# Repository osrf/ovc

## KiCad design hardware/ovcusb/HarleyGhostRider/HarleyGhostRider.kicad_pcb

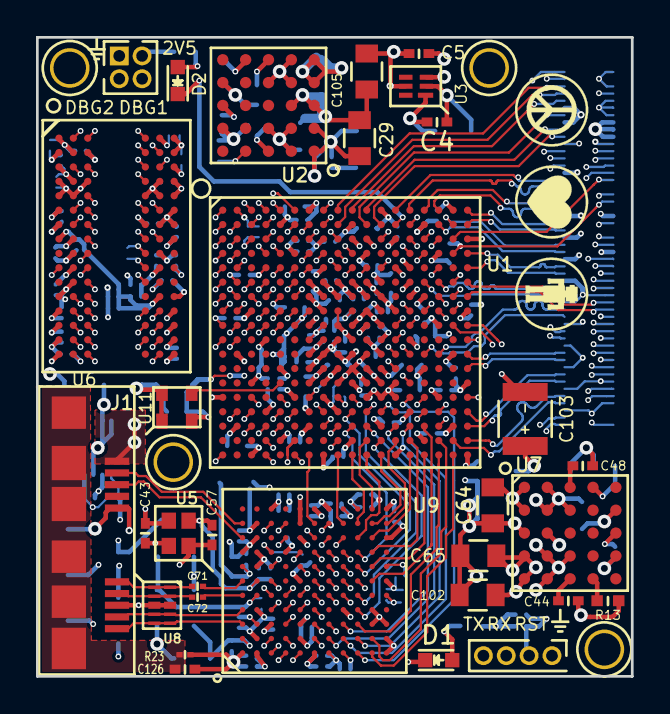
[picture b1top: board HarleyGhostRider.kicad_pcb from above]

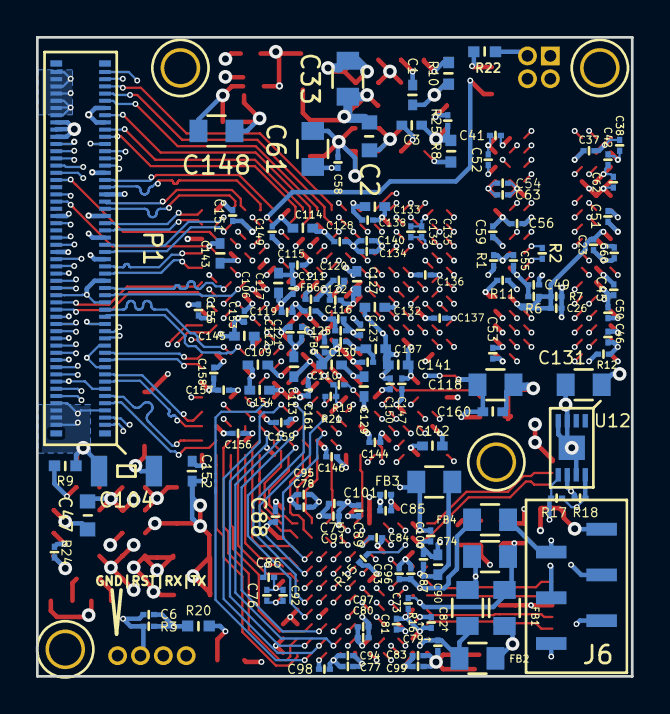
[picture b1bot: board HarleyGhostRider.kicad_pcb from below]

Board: 10 copper layers, 33.0 x 35.5 mm, 172 parts (141 on the bottom side), 210 nets.

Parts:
C1, C3, C44, C48, C160: 10n; C_0402
C2, C47: 10u; C_0603
C4, C5: 1u; C_0402
C6, C54, C56, C60, C111, C112, C115, C116, C117, C119, C120, C121, C122, C123, C124, C128, C130, C134, C135, C136, C137, C144, C146, C147, C149, C150, C151, C153, C155, C156, C157, C158, C159, C161: 470n; C_0201
C23, C58: 1u; C_0201
C26, C38, C42, C62, C63, C91, C92, C94, C95, C96, C97, C98, C99, C100, C101, C138, C139, C140: 10n; C_0201
C29, C33, C64, C65, C105, C118, C131, C148: 47u; C_0805
C37, C41, C45, C49, C51, C53: 2.2n; C_0201
C43, C57: 30p; C_0402
C46, C50, C52, C71, C72, C73, C75, C76, C77, C78, C79, C80, C81, C83, C84, C85, C86, C87, C88, C89, C93, C125: 100n; C_0201
C55: 3.3n; C_0201
C59: 4.7n; C_0201
C61, C74, C82, C102: 22u; C_0805
C90: 2.2u; C_0402
C103: 330u; C_1210Polarized
C104: 100u; C_1206
C106, C107, C109, C110, C113, C114, C127, C129, C132, C133, C141, C142, C143, C145, C152, C154: 4.7u; C_0402
C126: 4.7n; C_0402
D1: GREEN; LED_0603
D2: RED; LED_0603
FB1, FB2, FB3, FB4: 600; C_0805
FB5, FB6: 600; C_0201
J1: USB_3.1_microB; USB3_Micro-B
J3: CONN_01X04; Pin_Header_Straight_1x04_Pitch1.27mm
J6: CONN_01X06; GRPB061VWTC
P1: CONN_02X50; DF40C_100DP_0-4V
P2: CONN_02X02; Pin_Header_Straight_2x02_Pitch1.27mm
R1, R19, R21: 4.7k; C_0201
R2: 80.6; C_0201
R3, R17, R18: 10k; C_0201
R6, R7: 1k; C_0201
R8: 48.7k; R_0402
R9: 19.1k; R_0402
R10: 90.9k; R_0402
R11: 240; C_0201
R12: 2k; C_0201
R13: 60.4k; R_0402
R15: 6.04k; C_0201
R16: 200; C_0201
R20, R22: 200; R_0402
R23: 1M; C_0201
R24, R25: R; C_0201
U1: xc7a100tcsg324pkg; BGA324C80P18X18_1500X1500X150
U2, U7: LTM4622; LGA25_6.25X6.25X1.82
U3: TPS72718DSET; WSON6_15X15mm
U5: 8y-19.200MAAE; 8y
U6: MT41K128M16; WBGA96C80P6X16_800X1400X110
U8: IC10pins; 10-UFDFN
U9: CYUSB3014; BGA121C80P11X11_1000X1000X110
U11: OSCILLATOR; ASDMB
U12: 24LC128T-I/MNY; 8-TDFN_2x3_1EP

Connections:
+1V0: C33.2, C103.1, C104.1, C107.1, C110.1, C111.1, C113.1, C120.1, C121.1, C122.1, C123.1, C124.1, C127.1, C129.1, C130.1, C161.1, U1.F8, U1.F10, U1.G7, U1.G9, U1.G11, U1.H8, U1.J7, U1.J11, U1.K8, U1.L7, U1.L11, U1.M8, U1.M10, U1.N7, U1.N9, U1.N11, U2.D1, U2.E1
+1V2: C65.2, C76.1, C78.1, C81.1, C84.1, C86.1, C89.1, C92.1, C95.1, C98.1, C100.1, C102.1, FB1.1, FB2.1, FB3.1, U7.D1, U7.E1, U9.B10, U9.C3, U9.E9, U9.F11, U9.H1, U9.J11, U9.L5, U9.L7
+1V8: C5.1, C105.1, C106.1, C109.1, C112.1, C115.1, C117.1, C119.1, FB6.1, U1.F12, U1.H12, U1.K12, U1.M12, U3.5
+2V5: C4.1, C6.1, C64.2, C75.1, C77.1, C80.1, C83.1, C85.1, C88.1, C91.1, C94.1, C97.1, C99.1, C101.1, C114.1, C118.1, C128.1, C141.1, C142.1, C143.1, C144.1, C145.1, C146.1, C147.1, C148.1, C149.1, C150.1, C151.1, C152.1, C153.1, C154.1, C155.1, C156.1, C157.1, C158.1, C159.1, C160.1, FB4.1, J6.5, P1.82, P1.84, P1.86, P2.2, R3.1, R17.1, R18.1, R19.1, R20.1, R21.1, R22.1, U1.A17, U1.B10, U1.C13, U1.D16, U1.G15, U1.H18, U1.K4, U1.K14, U1.L17, U1.N3, U1.N13, U1.P6, U1.P8, U1.P11, U1.P12, U1.P13, U1.P16, U1.R9, U1.T2, U1.T12, U1.U5, U1.U15, U1.V8, U1.V18, U3.1, U3.3, U7.A1, U7.B1, U9.B1, U9.C11, U9.E3, U9.F1, U9.H4, U9.H11, U9.L9, U11.1, U11.4, U12.8
+5V: C2.2, C47.2, J1.1, P1.88, P1.90, P1.92, P1.94, P1.96, P1.98, P1.100, U2.A2, U2.B2, U2.B3, U2.D2, U2.D3, U2.E2, U7.A2, U7.B2, U7.B3, U7.D2, U7.D3, U7.E2, U9.E10, U9.E11
/Sheet56A15E50/AVDDQ: C87.1, C90.1, FB3.2, U9.A7
/Sheet56A15E50/CVDDQ: C93.1, C96.1, FB4.2, U9.B6
/Sheet56A15E50/USB_SS_TX+: C72.2, U9.A5
/Sheet56A15E50/USB_SS_TX-: C71.2, U9.A6
/Sheet56A15E50/VDDRX: C79.1, C82.1, FB2.2, U9.A2
/Sheet56A15E50/VDDTX: C73.1, C74.1, FB1.2, U9.B5
/Sheet56A15EBD/GND_ADC: FB5.1, U1.H9, U1.J9, U1.K10
Artix_FX3_CLK: U1.P3, U9.J6
DDR_A0: U1.G2, U6.N3
DDR_A1: U1.H5, U6.P7
DDR_A2: U1.G3, U6.P3
DDR_A3: U1.H2, U6.N2
DDR_A4: U1.J4, U6.P8
DDR_A5: U1.J2, U6.P2
DDR_A6: U1.G6, U6.R8
DDR_A7: U1.K1, U6.R2
DDR_A8: U1.H6, U6.T8
DDR_A9: U1.J3, U6.R3
DDR_A10: U1.F6, U6.L7
DDR_A11: U1.H4, U6.R7
DDR_A12: U1.G4, U6.N7
DDR_A13: U1.K2, U6.T3
DDR_BA0: U1.E1, U6.M2
DDR_BA1: U1.G1, U6.N8
DDR_BA2: U1.F1, U6.M3
DDR_CAS#: U1.C1, U6.K3
DDR_CKE: R1.1, U1.H1, U6.K9
DDR_CLK+: R2.1, U1.F4, U6.J7
DDR_CLK-: R2.2, U1.F3, U6.K7
DDR_DQL0: U1.B7, U6.E3
DDR_DQL1: U1.D8, U6.F7
DDR_DQL2: U1.C7, U6.F2
DDR_DQL3: U1.B6, U6.F8
DDR_DQL4: U1.E5, U6.H3
DDR_DQL5: U1.D7, U6.H8
DDR_DQL6: U1.E6, U6.G2
DDR_DQL7: U1.E7, U6.H7
DDR_DQSL+: U1.A6, U6.F3
DDR_DQSL-: U1.A5, U6.G3
DDR_DQSU+: U1.B1, U6.C7
DDR_DQSU-: U1.A1, U6.B7
DDR_DQU0: U1.B2, U6.D7
DDR_DQU1: U1.D4, U6.C3
DDR_DQU2: U1.B3, U6.C8
DDR_DQU3: U1.D5, U6.C2
DDR_DQU4: U1.B4, U6.A7
DDR_DQU5: U1.C4, U6.A2
DDR_DQU6: U1.A3, U6.B8
DDR_DQU7: U1.A4, U6.A3
DDR_ODT: U1.E2, U6.K1
DDR_RAS#: U1.C2, U6.J3
DDR_RST#: R12.2, U1.J5, U6.T2
DDR_VDD: C29.2, C37.1, C38.1, C41.1, C42.1, C45.1, C46.1, C49.1, C50.1, C51.1, C52.1, C53.1, C54.1, C55.1, C56.1, C58.1, C59.1, C60.1, C61.1, C62.1, C63.1, C131.1, C132.1, C133.1, C134.1, C135.1, C136.1, C137.1, C138.1, C139.1, C140.1, R6.1, R12.1, U1.A7, U1.C3, U1.D6, U1.F2, U1.G5, U1.J1, U2.A1, U2.B1, U6.A1, U6.A8, U6.B2, U6.C1, U6.C9, U6.D2, U6.D9, U6.E9, U6.F1, U6.G7, U6.H2, U6.H9, U6.K2, U6.K8, U6.N1, U6.N9, U6.R1, U6.R9
DDR_VREF: C23.1, C26.1, R6.2, R7.1, U6.H1, U6.M8
DDR_WE#: U1.D2, U6.L3
FLASH_SCL: R18.2, U9.D10, U12.6
FLASH_SDA: R17.2, U9.D9, U12.5
FPGA_CLK: U1.N5, U11.3
FPGA_DEBUG1: P2.4, U1.C9
FPGA_DEBUG2: P2.3, U1.D10
FPGA_JTAG_TCK: P1.54, U1.E10
FPGA_JTAG_TDI: P1.60, U1.E11
FPGA_JTAG_TDO: P1.58, U1.E13
FPGA_JTAG_TMS: P1.52, U1.E12
FPGA_LED: D2.1, U1.B13
FPGA_SS_CCLK: U1.E9, U9.D2
FPGA_SS_DIN: U1.K18, U9.D1
FPGA_SS_DONE: U1.P10, U9.C4
FPGA_SS_DOUT: U1.T16, U9.C1
FPGA_SS_INIT_B: R19.2, U1.P7, U9.D3
FPGA_SS_PROGRAM_B: R21.2, U1.P9, U9.D4
FPGA_Signal1: P1.64, U1.D17
FPGA_Signal2: P1.66, U1.E16
FPGA_Signal3: P1.70, U1.C17
FPGA_Signal4: P1.72, U1.D15
FPGA_Signal5: P1.74, U1.F14
FPGA_Signal6: P1.76, U1.C10
FPGA_Signal7: P1.78, U1.C12
FX3_A0: U1.T9, U9.H5
FX3_A1: U1.R11, U9.J5
FX3_DQ0: U1.V7, U9.F10
FX3_DQ1: U1.R3, U9.F9
FX3_DQ2: U1.R2, U9.F7
FX3_DQ3: U1.V4, U9.G10
FX3_DQ4: U1.T4, U9.G9
FX3_DQ5: U1.T3, U9.F8
FX3_DQ6: U1.V9, U9.H10
FX3_DQ7: U1.U6, U9.H9
FX3_DQ8: U1.V10, U9.J10
FX3_DQ9: U1.V11, U9.J9
FX3_DQ10: U1.U11, U9.K11
FX3_DQ11: U1.U13, U9.L10
FX3_DQ12: U1.V12, U9.K10
FX3_DQ13: U1.V14, U9.K9
FX3_DQ14: U1.T10, U9.J8
FX3_DQ15: U1.T5, U9.G8
FX3_DQ16: U1.U16, U9.K2
FX3_DQ17: U1.U12, U9.J4
FX3_DQ18: U1.V17, U9.K1
FX3_DQ19: U1.T14, U9.J2
FX3_DQ20: U1.V16, U9.J3
FX3_DQ21: U1.P14, U9.J1
FX3_DQ22: U1.R12, U9.H2
FX3_DQ23: U1.T11, U9.H3
FX3_DQ24: U1.P5, U9.F4
FX3_DQ25: U1.T13, U9.G2
FX3_DQ26: U1.R8, U9.G3
FX3_DQ27: U1.L14, U9.F3
FX3_DQ28: U1.U4, U9.F5
FX3_DQ29: U1.P18, U9.E1
FX3_DQ30: U1.V1, U9.E5
FX3_DQ31: U1.R16, U9.E4
FX3_FLAGA: U1.V6, U9.G7
FX3_FLAGB: U1.U9, U9.G6
FX3_FLAGC: U1.T15, U9.K6
FX3_FLAGD: U1.T8, U9.G5
FX3_JTAG_TCK: J6.1, U9.F6
FX3_JTAG_TDI: J6.2, U9.E7
FX3_JTAG_TDO: J6.4, U9.C10
FX3_JTAG_TMS: J6.3, U9.E8
FX3_LED/DEBUG: D1.1, U9.F2
FX3_PKT_END#: U1.R5, U9.H8
FX3_RST#: C6.2, J3.2, R3.2, U9.C5
FX3_SLCS#: U1.U14, U9.K8
FX3_SLOE#: U1.R10, U9.J7
FX3_SLRD#: U1.R6, U9.H7
FX3_SLWR#: U1.V15, U9.K7
FX3_UART_RX: J3.3, U9.D5
FX3_UART_TX: J3.4, U9.C2
GND: C1.2, C2.1, C3.2, C4.2, C5.2, C23.2, C26.2, C29.1, C33.1, C37.2, C38.2, C41.2, C42.2, C43.2, C44.2, C45.2, C46.2, C47.1, C48.2, C49.2, C50.2, C51.2, C52.2, C53.2, C54.2, C55.2, C56.2, C57.2, C58.2, C59.2, C60.2, C61.2, C62.2, C63.2, C64.1, C65.1, C73.2, C74.2, C75.2, C76.2, C77.2, C78.2, C79.2, C80.2, C81.2, C82.2, C83.2, C84.2, C85.2, C86.2, C87.2, C88.2, C89.2, C90.2, C91.2, C92.2, C93.2, C94.2, C95.2, C96.2, C97.2, C98.2, C99.2, C100.2, C101.2, C102.2, C103.2, C104.2, C105.2, C106.2, C107.2, C109.2, C110.2, C111.2, C112.2, C113.2, C114.2, C115.2, C116.2, C117.2, C118.2, C119.2, C120.2, C121.2, C122.2, C123.2, C124.2, C125.2, C126.2, C127.2, C128.2, C129.2, C130.2, C131.2, C132.2, C133.2, C134.2, C135.2, C136.2, C137.2, C138.2, C139.2, C140.2, C141.2, C142.2, C143.2, C144.2, C145.2, C146.2, C147.2, C148.2, C149.2, C150.2, C151.2, C152.2, C153.2, C154.2, C155.2, C156.2, C157.2, C158.2, C159.2, C160.2, C161.2, FB5.2, J1.5, J1.8, J3.1, J6.6, P1.2, P1.4, P1.5, P1.6, P1.8, P1.11, P1.14, P1.17, P1.20, P1.23, P1.26, P1.29, P1.32, P1.35, P1.38, P1.41, P1.44, P1.47, P1.50, P1.53, P1.59, P1.65, P1.71, P1.80, P1.85, P1.89, P2.1, R1.2, R7.2, R8.2, R9.2, R10.2, R11.2, R13.2, R15.2, R16.2, R23.2, R24.2, R25.2, U1.A2, U1.A12, U1.B5, U1.B15, U1.C8, U1.C18, U1.D1, U1.D11, U1.E4, U1.E8, U1.E14, U1.F7, U1.F9, U1.F11, U1.F17, U1.G8, U1.G10, U1.G12, U1.H3, U1.H7, U1.H11, U1.H13, U1.J6, U1.J8, U1.J10, U1.J12, U1.J16, U1.K7, U1.K9, U1.K11, U1.L2, U1.L8, U1.L9, U1.L10, U1.L12, U1.M5, U1.M7, U1.M9, U1.M11, U1.M15, U1.N8, U1.N10, U1.N12, U1.N18, U1.P1, U1.R4, U1.R14, U1.T7, U1.T17, U1.U10, U1.V3, U1.V13, U2.B5, U2.C1, U2.C2, U2.D5, U3.2, U5.2, U5.4, U6.A9, U6.B1, U6.B3, U6.B9, U6.D1, U6.D3, U6.D8, U6.E1, U6.E2, U6.E7, U6.E8, U6.F9, U6.G1, U6.G8, U6.G9, U6.J2, U6.J8, U6.L2, U6.M1, U6.M9, U6.P1, U6.P9, U6.T1, U6.T9, U7.B5, U7.C1, U7.C2, U7.D5, U8.3, U8.8, U9.A1, U9.A8, U9.B2, U9.B4, U9.B7, U9.B8, U9.B9, U9.D8, U9.E2, U9.E6, U9.G1, U9.G11, U9.K3, U9.K4, U9.L1, U9.L2, U9.L3, U9.L6, U9.L11, U11.2, U12.3, U12.4, U12.7, U12.EPAD
IMU_CS#: P1.77, U1.C16
unnamed: C1.1, U2.E3
unnamed: C3.1, U2.A3
unnamed: C43.1, U5.3, U9.C7
unnamed: C44.1, U7.E3
unnamed: C48.1, U7.A3
unnamed: C57.1, U5.1, U9.C6
unnamed: C116.1, C125.1, FB6.2, U1.H10
unnamed: C126.1, J1.SHLD, R23.1
unnamed: D1.2, R20.2
unnamed: D2.2, R22.2
unnamed: R8.1, U2.A4
unnamed: R9.1, U7.A4
unnamed: R10.1, U2.E4
unnamed: R11.1, U6.L8
unnamed: R13.1, U7.E4
unnamed: R15.1, U9.C8
unnamed: R16.1, U9.B3
unnamed: R24.1, U7.C5
unnamed: R25.1, U2.C5
Python1_CS#: P1.81, U1.B12
Python1_DOUT0+: P1.43, U1.E18
Python1_DOUT0-: P1.45, U1.D18
Python1_DOUT1+: P1.49, U1.B16
Python1_DOUT1-: P1.51, U1.B17
Python1_DOUT2+: P1.55, U1.B18
Python1_DOUT2-: P1.57, U1.A18
Python1_DOUT3+: P1.61, U1.A16
Python1_DOUT3-: P1.63, U1.A15
Python1_Monitor: P1.95, U1.A9
Python1_SYNC+: P1.67, U1.A14
Python1_SYNC-: P1.69, U1.A13
Python1_clk_return+: P1.37, U1.F15
Python1_clk_return-: P1.39, U1.F16
Python2_CS#: P1.83, U1.A11
Python2_DOUT0+: P1.18, U1.J18
Python2_DOUT0-: P1.16, U1.J17
Python2_DOUT1+: P1.12, U1.J13
Python2_DOUT1-: P1.10, U1.K13
Python2_DOUT2+: P1.22, U1.H17
Python2_DOUT2-: P1.24, U1.G17
Python2_DOUT3+: P1.28, U1.J14
Python2_DOUT3-: P1.30, U1.H15
Python2_Monitor: P1.97, U1.B8
Python2_SYNC+: P1.36, U1.F18
Python2_SYNC-: P1.34, U1.G18
Python2_clk_return+: P1.40, U1.H16
Python2_clk_return-: P1.42, U1.G16
Python3_CS#: P1.79, U1.B14
Python3_DOUT0+: P1.7, U1.U17
Python3_DOUT0-: P1.9, U1.U18
Python3_DOUT1+: P1.13, U1.T18
Python3_DOUT1-: P1.15, U1.R18
Python3_DOUT2+: P1.33, U1.L16
Python3_DOUT2-: P1.31, U1.L15
Python3_DOUT3+: P1.27, U1.L13
Python3_DOUT3-: P1.25, U1.M13
Python3_Monitor: P1.99, U1.A8
Python3_SYNC+: P1.21, U1.L18
Python3_SYNC-: P1.19, U1.M18
Python3_clk_return+: P1.3, U1.P15
Python3_clk_return-: P1.1, U1.R15
Python_RST#: P1.73, U1.D9
Python_Trigger: P1.75, U1.C15
Python_lvds_clk+: P1.46, U1.D14
Python_lvds_clk-: P1.48, U1.C14
SPI_MISO: P1.93, U1.B9
SPI_MOSI: P1.91, U1.A10
SPI_SCK: P1.87, U1.B11
SS_RX+: J1.10, U8.5, U8.6, U9.A3
SS_RX-: J1.9, U8.4, U8.7, U9.A4
SS_TX+: C72.1, J1.7, U8.2, U8.9
SS_TX-: C71.1, J1.6, U8.1, U8.10
USB_HS_D+: J1.3, U9.A9
USB_HS_D-: J1.2, U9.A10

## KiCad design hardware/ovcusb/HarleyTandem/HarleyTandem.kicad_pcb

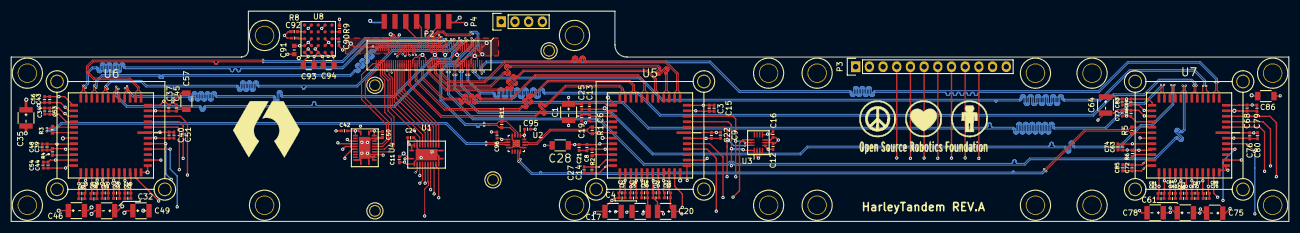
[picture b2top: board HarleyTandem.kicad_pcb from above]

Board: 6 copper layers, 237.0 x 39.0 mm, 115 parts (1 on the bottom side), 91 nets.

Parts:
C1, C4, C17, C20, C32, C35, C46, C49, C61, C64, C75, C78: 100u; C_1210Polarized
C2, C5, C7, C10, C15, C19, C21, C22, C25, C27, C30, C33, C36, C38, C41, C45, C48, C51, C53, C54, C56, C59, C62, C65, C67, C70, C74, C77, C79, C80, C83, C85, C88: 4.7u; C_0402
C3, C6, C8, C11, C12, C16, C24, C34, C37, C39, C42, C50, C63, C66, C68: 100n; C_0402
C9, C13, C14, C18, C23, C26, C29, C31, C40, C43, C44, C47, C52, C55, C58, C60, C69, C72, C73, C76, C81, C84, C87, C89, C95, C96: 1u; C_0402
C28, C57, C86: 10u; C_1206
C90, C92: 10n; C_0402
C91: 10u; C_0603
C93, C94: 47u; C_0805
P1: CONN_02X07; CustomJTAG
P2: CONN_02X50; DF40C_100DS_0-4V
P3: CONN_01X12; Pin_Header_Straight_1x12
P4: CONN_01X04; Pin_Header_Straight_1x04
R1, R3, R5, R11: 100; R_0402
R2, R4, R6: 47k; R_0402
R8: 13.3k; R_0402
R9: 30.1k; R_0402
U1, U4: 74AVCH8T245-1EP; QFN-24-1EP-Pitch0.5-nonSquare
U2: SI53306; QFN-16-1EP_3x3mm_Pitch0.5mm
U3: ST_LSM6DS3; LGA14_2.5X3X0.86
U5, U6, U7: NOIP1SN1300A-QDI; LCC101.6P1422X1422X165-48
U8: LTM4622; LGA25_6.25X6.25X1.82

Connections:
+1V8: C3.1, C6.1, C8.1, C15.1, C16.1, C19.1, C21.1, C28.1, C34.1, C37.1, C39.1, C45.1, C48.1, C53.1, C57.1, C63.1, C66.1, C68.1, C74.1, C77.1, C79.1, C86.1, C94.2, P4.3, U3.8, U5.6, U5.22, U5.26, U6.6, U6.22, U6.26, U7.6, U7.22, U7.26, U8.D1, U8.E1
+2V5: C24.1, C50.1, C95.2, C96.1, P1.2, P2.81, P2.83, P2.85, P3.3, U1.23, U1.24, U2.1, U2.5, U2.16, U4.23, U4.24
+3V3: C1.1, C2.1, C4.1, C5.1, C7.1, C9.1, C10.1, C11.1, C12.1, C13.1, C14.1, C17.1, C18.1, C20.1, C22.1, C23.1, C25.1, C26.1, C27.1, C29.1, C30.1, C31.1, C32.1, C33.1, C35.1, C36.1, C38.1, C40.1, C41.1, C42.1, C43.1, C44.1, C46.1, C47.1, C49.1, C51.1, C52.1, C54.1, C55.1, C56.1, C58.1, C59.1, C60.1, C61.1, C62.1, C64.1, C65.1, C67.1, C69.1, C70.1, C72.1, C73.1, C75.1, C76.1, C78.1, C80.1, C81.1, C83.1, C84.1, C85.1, C87.1, C88.1, C89.1, C93.2, P3.2, P4.2, U1.1, U3.5, U4.1, U4.2, U5.1, U5.19, U5.29, U5.31, U5.33, U5.36, U5.38, U5.40, U6.1, U6.19, U6.29, U6.31, U6.33, U6.36, U6.38, U6.40, U7.1, U7.19, U7.29, U7.31, U7.33, U7.36, U7.38, U7.40, U8.A1, U8.B1
+5V: C91.2, P2.87, P2.89, P2.91, P2.93, P2.95, P2.97, P2.99, P3.1, P4.1, U8.A2, U8.B2, U8.B3, U8.D2, U8.D3, U8.E2
FPGA_JTAG_TCK: P1.6, P2.53
FPGA_JTAG_TDI: P1.10, P2.59
FPGA_JTAG_TDO: P1.8, P2.57
FPGA_JTAG_TMS: P1.4, P2.51
FPGA_Signal1: P2.63, P3.4
FPGA_Signal2: P2.65, P3.5
FPGA_Signal3: P2.69, P3.6
FPGA_Signal4: P2.71, P3.7
FPGA_Signal5: P2.73, P3.8
FPGA_Signal6: P2.75, P3.9
FPGA_Signal7: P2.77, P3.10
GND: C1.2, C2.2, C3.2, C4.2, C5.2, C6.2, C7.2, C8.2, C9.2, C10.2, C11.2, C12.2, C13.2, C14.2, C15.2, C16.2, C17.2, C18.2, C19.2, C20.2, C21.2, C22.2, C23.2, C24.2, C25.2, C26.2, C27.2, C28.2, C29.2, C30.2, C31.2, C32.2, C33.2, C34.2, C35.2, C36.2, C37.2, C38.2, C39.2, C40.2, C41.2, C42.2, C43.2, C44.2, C45.2, C46.2, C47.2, C48.2, C49.2, C50.2, C51.2, C52.2, C53.2, C54.2, C55.2, C56.2, C57.2, C58.2, C59.2, C60.2, C61.2, C62.2, C63.2, C64.2, C65.2, C66.2, C67.2, C68.2, C69.2, C70.2, C72.2, C73.2, C74.2, C75.2, C76.2, C77.2, C78.2, C79.2, C80.2, C81.2, C83.2, C84.2, C85.2, C86.2, C87.2, C88.2, C89.2, C90.2, C91.1, C92.2, C93.1, C94.1, C95.1, C96.2, P1.1, P1.3, P1.5, P1.7, P1.9, P1.11, P1.13, P2.1, P2.3, P2.5, P2.6, P2.7, P2.12, P2.13, P2.18, P2.19, P2.24, P2.25, P2.30, P2.31, P2.36, P2.37, P2.42, P2.43, P2.48, P2.49, P2.54, P2.60, P2.66, P2.72, P2.79, P2.86, P2.90, P3.11, P3.12, P4.4, R2.2, R4.2, R6.2, R8.2, R9.2, U1.2, U1.11, U1.12, U1.13, U1.22, U1.25, U2.4, U2.8, U2.13, U2.17, U3.2, U3.3, U3.6, U3.7, U4.11, U4.12, U4.13, U4.14, U4.15, U4.16, U4.21, U4.22, U4.25, U5.5, U5.20, U5.21, U5.25, U5.27, U5.30, U5.32, U5.34, U5.35, U5.37, U5.39, U5.42, U5.43, U5.48, U6.5, U6.20, U6.21, U6.25, U6.27, U6.30, U6.32, U6.34, U6.35, U6.37, U6.39, U6.42, U6.43, U6.48, U7.5, U7.20, U7.21, U7.25, U7.27, U7.30, U7.32, U7.34, U7.35, U7.37, U7.39, U7.42, U7.43, U7.48, U8.B5, U8.C1, U8.C2, U8.D5
IMU_CS#: P2.78, U1.16
IMU_CS#_3V3: U1.8, U3.12
unnamed: C90.1, U8.E3
unnamed: C92.1, U8.A3
unnamed: R2.1, U5.28
unnamed: R4.1, U6.28
unnamed: R6.1, U7.28
unnamed: R8.1, U8.A4
unnamed: R9.1, U8.E4
Python1_CS#: P2.82, U1.18
Python1_CS#_3V3: U1.6, U5.47
Python1_DOUT0+: P2.44, U5.9
Python1_DOUT0-: P2.46, U5.10
Python1_DOUT1+: P2.50, U5.11
Python1_DOUT1-: P2.52, U5.12
Python1_DOUT2+: P2.56, U5.13
Python1_DOUT2-: P2.58, U5.14
Python1_DOUT3+: P2.62, U5.15
Python1_DOUT3-: P2.64, U5.16
Python1_Monitor: P2.96, U4.18
Python1_Monitor_3V3: U4.6, U5.44
Python1_SYNC+: P2.68, U5.17
Python1_SYNC-: P2.70, U5.18
Python1_clk_return+: P2.38, U5.7
Python1_clk_return-: P2.40, U5.8
Python1_lvds_clk+: R1.2, U2.14, U5.24
Python1_lvds_clk-: R1.1, U2.15, U5.23
Python2_CS#: P2.84, U1.19
Python2_CS#_3V3: U1.5, U6.47
Python2_DOUT0+: P2.17, U6.9
Python2_DOUT0-: P2.15, U6.10
Python2_DOUT1+: P2.11, U6.11
Python2_DOUT1-: P2.9, U6.12
Python2_DOUT2+: P2.21, U6.13
Python2_DOUT2-: P2.23, U6.14
Python2_DOUT3+: P2.27, U6.15
Python2_DOUT3-: P2.29, U6.16
Python2_Monitor: P2.98, U4.19
Python2_Monitor_3V3: U4.5, U6.44
Python2_SYNC+: P2.35, U6.17
Python2_SYNC-: P2.33, U6.18
Python2_clk_return+: P2.39, U6.7
Python2_clk_return-: P2.41, U6.8
Python2_lvds_clk+: R3.2, U2.7, U6.24
Python2_lvds_clk-: R3.1, U2.6, U6.23
Python3_CS#: P2.80, U1.17
Python3_CS#_3V3: U1.7, U7.47
Python3_DOUT0+: P2.8, U7.9
Python3_DOUT0-: P2.10, U7.10
Python3_DOUT1+: P2.14, U7.11
Python3_DOUT1-: P2.16, U7.12
Python3_DOUT2+: P2.34, U7.13
Python3_DOUT2-: P2.32, U7.14
Python3_DOUT3+: P2.28, U7.15
Python3_DOUT3-: P2.26, U7.16
Python3_Monitor: P2.100, U4.20
Python3_Monitor_3V3: U4.4, U7.44
Python3_SYNC+: P2.22, U7.17
Python3_SYNC-: P2.20, U7.18
Python3_clk_return+: P2.4, U7.7
Python3_clk_return-: P2.2, U7.8
Python3_lvds_clk+: R5.2, U2.11, U7.24
Python3_lvds_clk-: R5.1, U2.12, U7.23
Python_RST#: P2.74, U1.14
Python_RST#_3V3: U1.10, U5.46, U6.46, U7.46
Python_Trigger: P2.76, U1.15
Python_Trigger_3V3: U1.9, U5.41, U6.41, U7.41
Python_lvds_clk+: P2.45, R11.2, U2.3
Python_lvds_clk-: P2.47, R11.1, U2.2
SPI_MISO: P2.94, U4.17
SPI_MISO_3V3: U3.1, U4.7, U5.3, U6.3, U7.3
SPI_MOSI: P2.92, U1.21
SPI_MOSI_3V3: U1.3, U3.14, U5.2, U6.2, U7.2
SPI_SCK: P2.88, U1.20
SPI_SCK_3V3: U1.4, U3.13, U5.4, U6.4, U7.4

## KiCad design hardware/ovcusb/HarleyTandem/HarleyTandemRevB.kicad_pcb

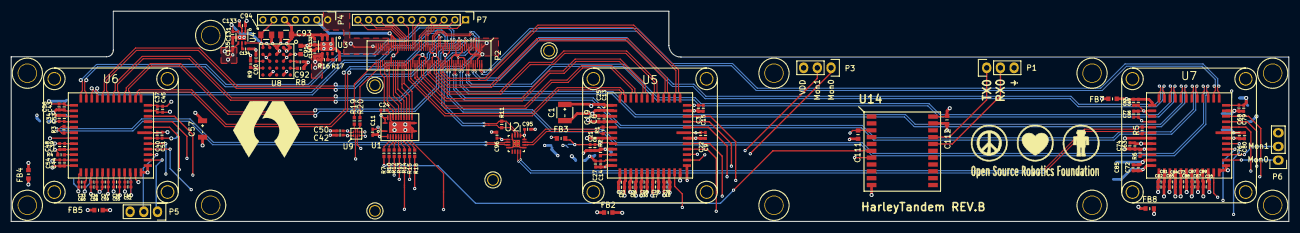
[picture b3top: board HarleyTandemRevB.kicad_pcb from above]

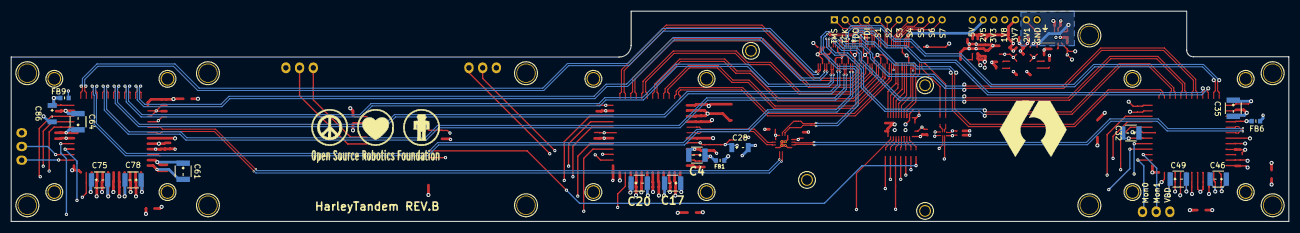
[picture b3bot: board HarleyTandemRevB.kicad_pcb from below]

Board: 6 copper layers, 237.0 x 39.0 mm, 146 parts (16 on the bottom side), 117 nets.

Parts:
C1, C4, C17, C20, C32, C35, C46, C49, C61, C64, C75, C78: 100u; C_1210Polarized
C2, C5, C7, C10, C15, C19, C21, C22, C25, C27, C30, C33, C36, C38, C41, C45, C48, C51, C53, C54, C56, C59, C62, C65, C67, C70, C74, C77, C79, C80, C83, C85, C88: 4.7u; C_0402
C3, C6, C8, C11, C24, C34, C37, C39, C42, C50, C63, C66, C68: 100n; C_0402
C9, C13, C14, C18, C23, C26, C29, C31, C40, C43, C44, C47, C52, C55, C58, C60, C69, C72, C73, C76, C81, C84, C87, C89, C95, C96, C131, C132, C133, C135: 1u; C_0402
C28, C57, C86: 10u; C_1206_Polarized
C90, C92, C134: 10n; C_0402
C91: 10u; C_0603
C93, C94: 47u; C_0805
C111, C112: 100n; C_0603
C136: 2.2u; C_0402
FB1, FB3, FB4, FB6, FB7, FB9: 220; R_0603
FB2, FB5, FB8: 1k; R_0603
P1, P3, P5, P6: CONN_01X03; Pin_Header_Straight_1x03
P2: CONN_02X50; DF40C_100DS_0-4V
P4: CONN_01X07; Pin_Header_Straight_1x07_Pitch2.00mm
P7: CONN_01X11; Pin_Header_Straight_1x11_Pitch2.00mm
R1, R3, R5, R11: 100; R_0402
R2, R4, R6: 47k; R_0402
R7, R10, R12, R13, R14, R15, R18, R19, R20: 49.9; R_0402
R8: 11.5k; R_0402
R9: 24k; R_0402
R16: 8.06k; R_0402
R17: 4.7k; R_0402
U1: 74AVCH8T245-1EP; QFN-24-1EP-Pitch0.5-nonSquare
U2: SI53306; QFN-16-1EP_3x3mm_Pitch0.5mm
U3: LD39150PU; DFN-6-1EP_3x3mm_Pitch0.95mm
U4: mic5325; DFN-6-1EP_2x2mm_Pitch0.65mm
U5, U6, U7: NOIP1SN1300A-QDI; LCC101.6P1422X1422X165-48
U8: LTM4622; LGA25_6.25X6.25X1.82
U9: SN74AVC2T244; SON-N8-145x105
U14: uIMU-2; DFP-22_0.5mmPitch_125x155mm

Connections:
2V1: C94.2, C131.1, P4.6, U4.3, U4.6, U8.D1, U8.E1
3V7: C93.2, C132.1, P4.5, U3.2, U3.3, U8.A1, U8.B1
+1V8: C135.1, FB3.1, FB6.1, FB9.1, P4.4, U4.4
+2V5: C24.1, C50.1, C95.2, C96.1, P2.81, P2.83, P2.85, P4.2, U1.23, U1.24, U2.1, U2.5, U2.16, U9.8
+3V3: C11.1, C42.1, C111.1, C112.1, C133.1, C136.1, FB1.1, FB2.1, FB4.1, FB5.1, FB7.1, FB8.1, P4.3, R16.1, U1.1, U3.4, U4.1, U9.1, U14.3, U14.22
+5V: C91.2, P2.87, P2.89, P2.91, P2.93, P2.95, P2.97, P2.99, P4.1, U8.A2, U8.B2, U8.B3, U8.D2, U8.D3, U8.E2
FPGA_JTAG_TCK: P2.53, P7.2
FPGA_JTAG_TDI: P2.59, P7.4
FPGA_JTAG_TDO: P2.57, P7.3
FPGA_JTAG_TMS: P2.51, P7.1
FPGA_Signal1: P2.63, P7.5
FPGA_Signal2: P2.65, P7.6
FPGA_Signal3: P2.69, P7.7
FPGA_Signal4: P2.71, P7.8
FPGA_Signal5: P2.73, P7.9
FPGA_Signal6: P2.75, P7.10
FPGA_Signal7: P2.77, P7.11
GND: C1.2, C2.2, C3.2, C4.2, C5.2, C6.2, C7.2, C8.2, C9.2, C10.2, C11.2, C13.2, C14.2, C15.2, C17.2, C18.2, C19.2, C20.2, C21.2, C22.2, C23.2, C24.2, C25.2, C26.2, C27.2, C28.2, C29.2, C30.2, C31.2, C32.2, C33.2, C34.2, C35.2, C36.2, C37.2, C38.2, C39.2, C40.2, C41.2, C42.2, C43.2, C44.2, C45.2, C46.2, C47.2, C48.2, C49.2, C50.2, C51.2, C52.2, C53.2, C54.2, C55.2, C56.2, C57.2, C58.2, C59.2, C60.2, C61.2, C62.2, C63.2, C64.2, C65.2, C66.2, C67.2, C68.2, C69.2, C70.2, C72.2, C73.2, C74.2, C75.2, C76.2, C77.2, C78.2, C79.2, C80.2, C81.2, C83.2, C84.2, C85.2, C86.2, C87.2, C88.2, C89.2, C90.2, C91.1, C92.2, C93.1, C94.1, C95.1, C96.2, C111.2, C112.2, C131.2, C132.2, C133.2, C134.2, C135.2, C136.2, P1.3, P2.1, P2.3, P2.5, P2.6, P2.7, P2.12, P2.13, P2.18, P2.19, P2.24, P2.25, P2.30, P2.31, P2.36, P2.37, P2.42, P2.43, P2.48, P2.49, P2.54, P2.60, P2.66, P2.72, P2.79, P2.86, P2.90, P4.7, R2.2, R4.2, R6.2, R8.2, R9.2, R17.2, U1.2, U1.11, U1.12, U1.13, U1.22, U1.25, U2.4, U2.8, U2.13, U2.17, U3.1, U3.7, U4.2, U4.7, U5.5, U5.20, U5.21, U5.25, U5.27, U5.30, U5.32, U5.34, U5.35, U5.37, U5.39, U5.42, U5.43, U5.48, U6.5, U6.20, U6.21, U6.25, U6.27, U6.30, U6.32, U6.34, U6.35, U6.37, U6.39, U6.42, U6.43, U6.48, U7.5, U7.20, U7.21, U7.25, U7.27, U7.30, U7.32, U7.34, U7.35, U7.37, U7.39, U7.42, U7.43, U7.48, U8.B5, U8.C1, U8.C2, U8.D5, U9.4, U9.5, U14.11, U14.21
IMU_RX0: P1.2, U14.18
IMU_RX1: R7.2, U14.6
IMU_RX1_2V5: P2.96, U1.21
IMU_TX0: P1.1, U14.19
IMU_TX1: U9.3, U14.7
IMU_TX1_2V5: P2.98, R20.1
unnamed: C90.1, U8.E3
unnamed: C92.1, U8.A3
unnamed: C134.1, U4.5
unnamed: R2.1, U5.28
unnamed: R4.1, U6.28
unnamed: R6.1, U7.28
unnamed: R7.1, U1.3
unnamed: R8.1, U8.A4
unnamed: R9.1, U8.E4
unnamed: R10.1, U1.4
unnamed: R12.1, U1.5
unnamed: R13.1, U1.6
unnamed: R14.1, U1.7
unnamed: R15.1, U1.8
unnamed: R16.2, R17.1, U3.5
unnamed: R18.1, U1.9
unnamed: R19.2, U9.7
unnamed: R20.2, U9.6
Python1_1V8: C3.1, C6.1, C8.1, C15.1, C19.1, C21.1, C28.1, FB3.2, U5.6, U5.22, U5.26
Python1_CS#: P2.80, U1.16
Python1_CS#_3V3: R15.2, U5.47
Python1_DOUT0+: P2.44, U5.9
Python1_DOUT0-: P2.46, U5.10
Python1_DOUT1+: P2.50, U5.11
Python1_DOUT1-: P2.52, U5.12
Python1_DOUT2+: P2.56, U5.13
Python1_DOUT2-: P2.58, U5.14
Python1_DOUT3+: P2.62, U5.15
Python1_DOUT3-: P2.64, U5.16
Python1_Monitor0_3V3: P3.1, U5.44
Python1_Monitor1_3V3: P3.2, U5.45
Python1_SYNC+: P2.68, U5.17
Python1_SYNC-: P2.70, U5.18
Python1_VDD: C1.1, C4.1, C9.1, C13.1, C14.1, C18.1, C22.1, C25.1, C27.1, C30.1, FB1.2, P3.3, U5.1, U5.19, U5.29, U5.36
Python1_VDDPIX: C2.1, C5.1, C7.1, C10.1, C17.1, C20.1, C23.1, C26.1, C29.1, C31.1, FB2.2, U5.31, U5.33, U5.38, U5.40
Python1_clk_return+: P2.38, U5.7
Python1_clk_return-: P2.40, U5.8
Python1_lvds_clk+: R1.2, U2.14, U5.24
Python1_lvds_clk-: R1.1, U2.15, U5.23
Python2_1V8: C34.1, C37.1, C39.1, C45.1, C48.1, C53.1, C57.1, FB6.2, U6.6, U6.22, U6.26
Python2_CS#: P2.84, U1.18
Python2_CS#_3V3: R13.2, U6.47
Python2_DOUT0+: P2.9, U6.9
Python2_DOUT0-: P2.11, U6.10
Python2_DOUT1+: P2.15, U6.11
Python2_DOUT1-: P2.17, U6.12
Python2_DOUT2+: P2.21, U6.13
Python2_DOUT2-: P2.23, U6.14
Python2_DOUT3+: P2.33, U6.15
Python2_DOUT3-: P2.35, U6.16
Python2_Monitor0_3V3: P5.1, U6.44
Python2_Monitor1_3V3: P5.2, U6.45
Python2_SYNC+: P2.29, U6.17
Python2_SYNC-: P2.27, U6.18
Python2_VDD: C32.1, C35.1, C40.1, C43.1, C44.1, C47.1, C51.1, C54.1, C56.1, C59.1, FB4.2, P5.3, U6.1, U6.19, U6.29, U6.36
Python2_VDDPIX: C33.1, C36.1, C38.1, C41.1, C46.1, C49.1, C52.1, C55.1, C58.1, C60.1, FB5.2, U6.31, U6.33, U6.38, U6.40
Python2_clk_return+: P2.39, U6.7
Python2_clk_return-: P2.41, U6.8
Python2_lvds_clk+: R3.2, U2.7, U6.24
Python2_lvds_clk-: R3.1, U2.6, U6.23
Python3_1V8: C63.1, C66.1, C68.1, C74.1, C77.1, C79.1, C86.1, FB9.2, U7.6, U7.22, U7.26
Python3_CS#: P2.82, U1.17
Python3_CS#_3V3: R14.2, U7.47
Python3_DOUT0+: P2.34, U7.9
Python3_DOUT0-: P2.32, U7.10
Python3_DOUT1+: P2.28, U7.11
Python3_DOUT1-: P2.26, U7.12
Python3_DOUT2+: P2.22, U7.13
Python3_DOUT2-: P2.20, U7.14
Python3_DOUT3+: P2.16, U7.15
Python3_DOUT3-: P2.14, U7.16
Python3_Monitor0_3V3: P6.1, U7.44
Python3_Monitor1_3V3: P6.2, U7.45
Python3_SYNC+: P2.10, U7.17
Python3_SYNC-: P2.8, U7.18
Python3_VDD: C61.1, C64.1, C69.1, C72.1, C73.1, C76.1, C80.1, C83.1, C85.1, C88.1, FB7.2, P6.3, U7.1, U7.19, U7.29, U7.36
Python3_VDDPIX: C62.1, C65.1, C67.1, C70.1, C75.1, C78.1, C81.1, C84.1, C87.1, C89.1, FB8.2, U7.31, U7.33, U7.38, U7.40
Python3_clk_return+: P2.2, U7.7
Python3_clk_return-: P2.4, U7.8
Python3_lvds_clk+: R5.2, U2.11, U7.24
Python3_lvds_clk-: R5.1, U2.12, U7.23
Python_RST#: P2.74, U1.14
Python_RST#_3V3: U1.10, U5.46, U6.46, U7.46
Python_Trigger: P2.76, U1.15
Python_Trigger_3V3: R18.2, U5.41, U6.41, U7.41
Python_lvds_clk+: P2.45, R11.2, U2.3
Python_lvds_clk-: P2.47, R11.1, U2.2
SPI_MISO: P2.100, R19.1
SPI_MISO_3V3: U5.3, U6.3, U7.3, U9.2
SPI_MOSI: P2.92, U1.20
SPI_MOSI_3V3: R10.2, U5.2, U6.2, U7.2
SPI_SCK: P2.88, U1.19
SPI_SCK_3V3: R12.2, U5.4, U6.4, U7.4
